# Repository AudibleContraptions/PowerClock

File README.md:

# AudibleContraptions PowerClock

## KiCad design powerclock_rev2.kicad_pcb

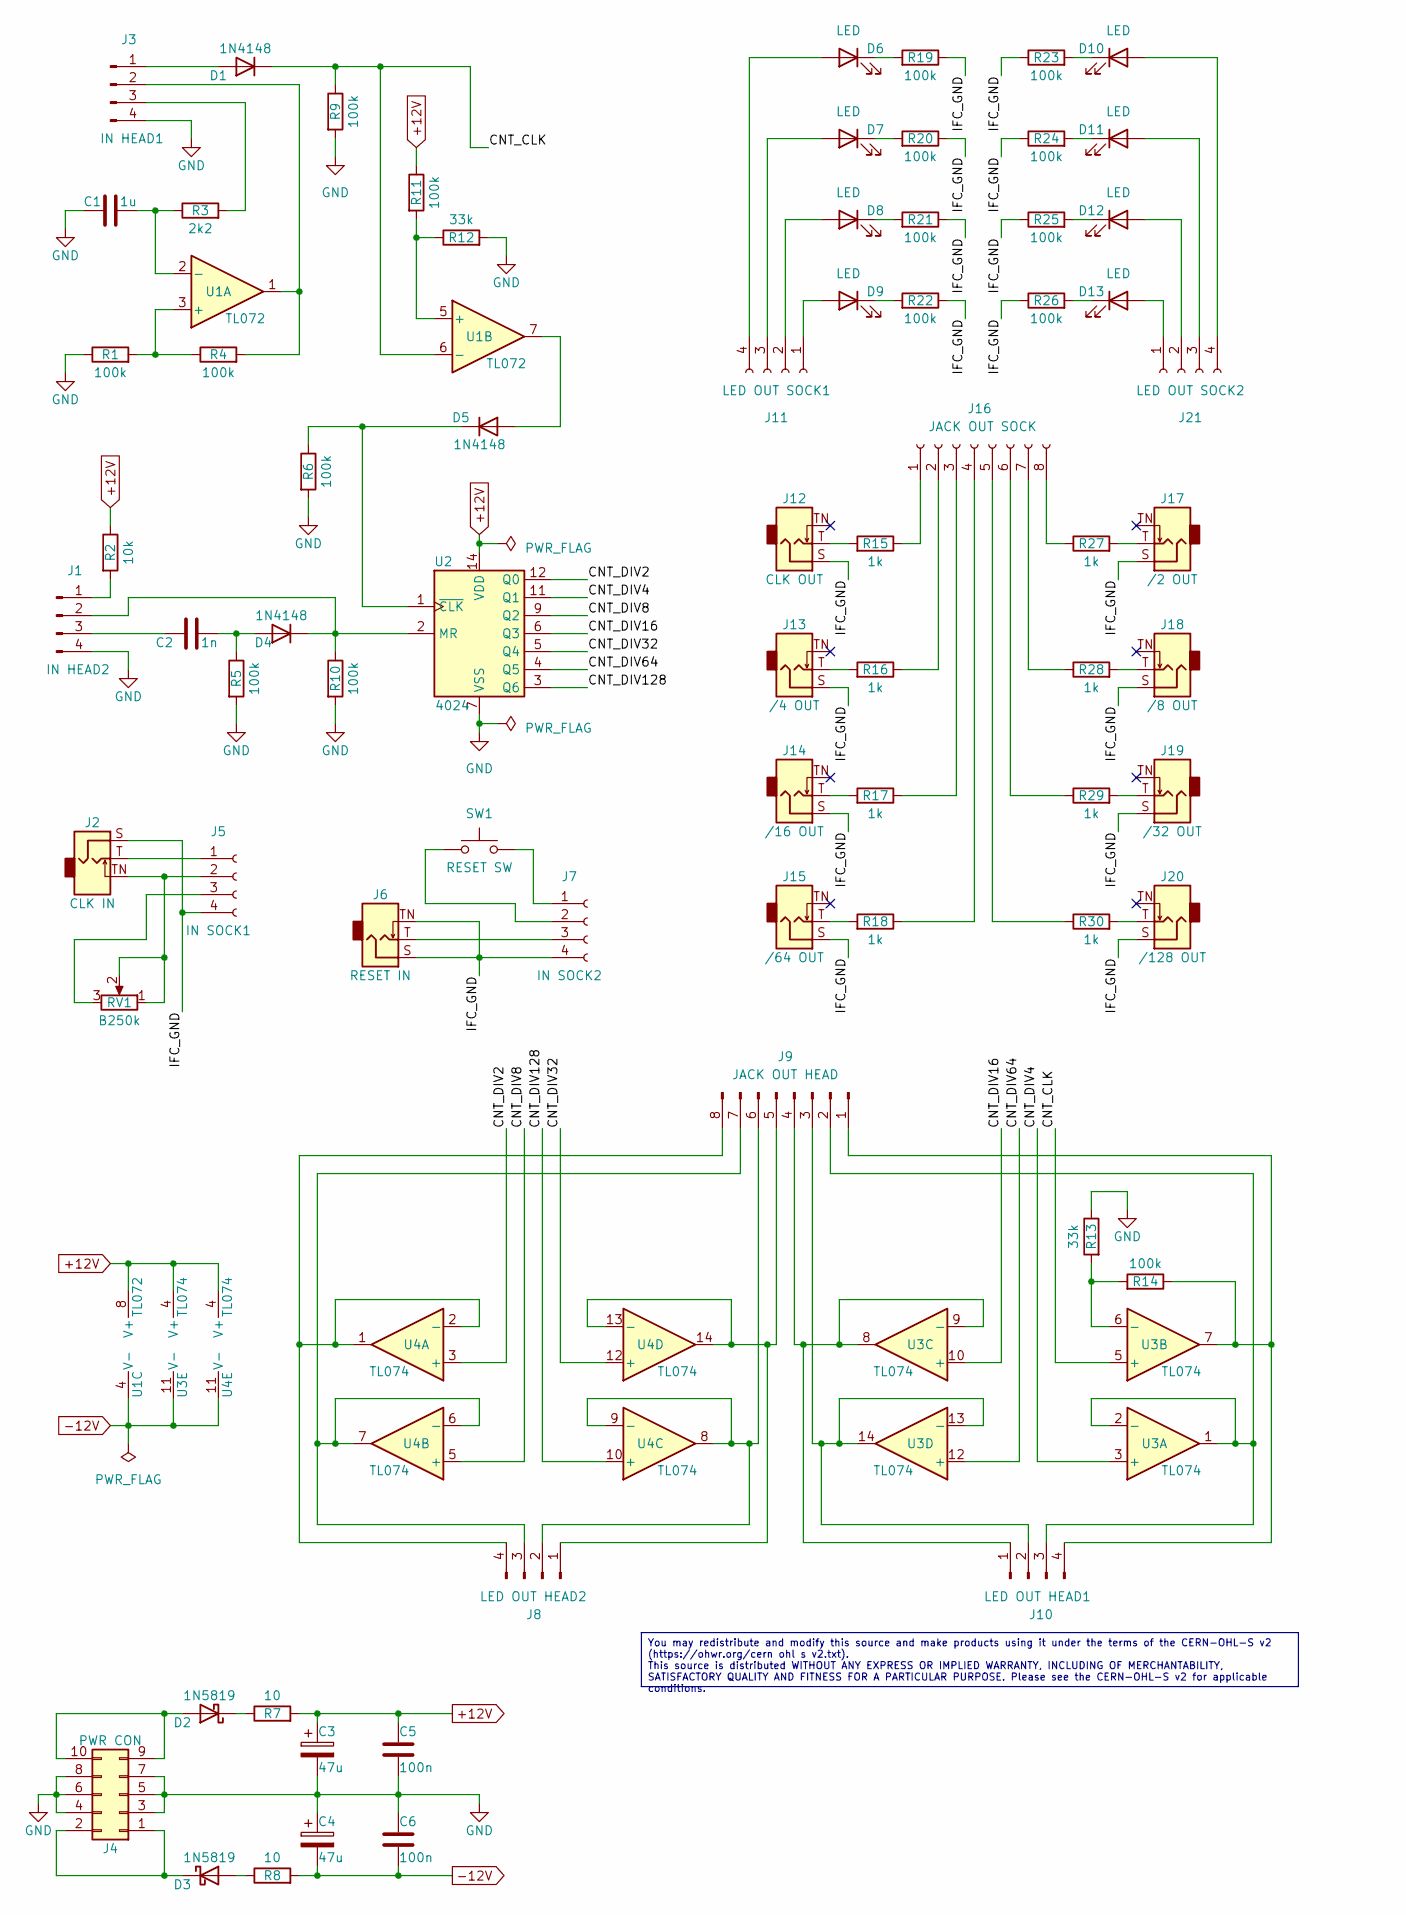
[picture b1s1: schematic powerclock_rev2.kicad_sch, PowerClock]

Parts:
C1: 1u; C_Disc_D4.3mm_W1.9mm_P5.00mm
C2: 1n; C_Disc_D4.3mm_W1.9mm_P5.00mm
C3, C4: 47u; C_Radial_D5.0mm_H11.0mm_P2.00mm
C5, C6: 100n; C_Disc_D4.3mm_W1.9mm_P5.00mm
D1, D4, D5: 1N4148; D_DO-35_SOD27_P7.62mm_Horizontal
D2, D3: 1N5819; D_DO-41_SOD81_P10.16mm_Horizontal
D6, D7, D8, D9, D10, D11, D12, D13: LED; LED_D3.0mm
J1: IN HEAD2; PinHeader_2x02_P2.54mm_Vertical
J2: CLK IN; Jack_3.5mm_QingPu_WQP-PJ398SM_Vertical_CircularHoles
J3: IN HEAD1; PinHeader_2x02_P2.54mm_Vertical
J4: PWR CON; PinHeader_2x05_P2.54mm_Vertical
J5: IN SOCK1; PinSocket_2x02_P2.54mm_Vertical
J6: RESET IN; Jack_3.5mm_QingPu_WQP-PJ398SM_Vertical_CircularHoles
J7: IN SOCK2; PinSocket_2x02_P2.54mm_Vertical
J8: LED OUT HEAD2; PinHeader_1x04_P2.54mm_Vertical
J9: JACK OUT HEAD; PinHeader_1x08_P2.54mm_Vertical
J10: LED OUT HEAD1; PinHeader_1x04_P2.54mm_Vertical
J11: LED OUT SOCK1; PinSocket_1x04_P2.54mm_Vertical
J12: CLK OUT; Jack_3.5mm_QingPu_WQP-PJ398SM_Vertical_CircularHoles
J13: /4 OUT; Jack_3.5mm_QingPu_WQP-PJ398SM_Vertical_CircularHoles
J14: /16 OUT; Jack_3.5mm_QingPu_WQP-PJ398SM_Vertical_CircularHoles
J15: /64 OUT; Jack_3.5mm_QingPu_WQP-PJ398SM_Vertical_CircularHoles
J16: JACK OUT SOCK; PinSocket_1x08_P2.54mm_Vertical
J17: /2 OUT; Jack_3.5mm_QingPu_WQP-PJ398SM_Vertical_CircularHoles
J18: /8 OUT; Jack_3.5mm_QingPu_WQP-PJ398SM_Vertical_CircularHoles
J19: /32 OUT; Jack_3.5mm_QingPu_WQP-PJ398SM_Vertical_CircularHoles
J20: /128 OUT; Jack_3.5mm_QingPu_WQP-PJ398SM_Vertical_CircularHoles
J21: LED OUT SOCK2; PinSocket_1x04_P2.54mm_Vertical
R1, R4, R5, R6, R9, R10, R11, R14, R19, R20, R21, R22, R23, R24, R25, R26: 100k; R_Axial_DIN0207_L6.3mm_D2.5mm_P7.62mm_Horizontal
R2: 10k; R_Axial_DIN0207_L6.3mm_D2.5mm_P7.62mm_Horizontal
R3: 2k2; R_Axial_DIN0207_L6.3mm_D2.5mm_P7.62mm_Horizontal
R7, R8: 10; R_Axial_DIN0207_L6.3mm_D2.5mm_P7.62mm_Horizontal
R12, R13: 33k; R_Axial_DIN0207_L6.3mm_D2.5mm_P7.62mm_Horizontal
R15, R16, R17, R18, R27, R28, R29, R30: 1k; R_Axial_DIN0207_L6.3mm_D2.5mm_P7.62mm_Horizontal
RV1: B250k; Potentiometer_Alpha_RD901F-40-00D_Single_Vertical
SW1: RESET SW; SW_PUSH_6mm
U1: TL072; DIP-8_W7.62mm_Socket
U2: 4024; DIP-14_W7.62mm_Socket
U3, U4: TL074; DIP-14_W7.62mm_Socket

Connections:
+12V: C3.1, C5.2, R2.1, R7.2, R11.1, U1.8 (V+), U2.14 (VDD), U3.4 (V+), U4.4 (V+)
-12V: C4.2, C6.1, R8.2, U1.4 (V-), U3.11 (V-), U4.11 (V-)
/CNT_CLK: D1.1 (K), R9.1, U1.6 (-), U3.5 (+)
/CNT_DIV2: U2.12 (Q0), U4.3 (+)
/CNT_DIV4: U2.11 (Q1), U3.3 (+)
/CNT_DIV8: U2.9 (Q2), U4.5 (+)
/CNT_DIV16: U2.6 (Q3), U3.10 (+)
/CNT_DIV32: U2.5 (Q4), U4.12 (+)
/CNT_DIV64: U2.4 (Q5), U3.12 (+)
/CNT_DIV128: U2.3 (Q6), U4.10 (+)
/IFC_GND: J2.S, J5.4, J6.S, J6.TN, J7.4, J12.S, J13.S, J14.S, J15.S, J17.S, J18.S, J19.S, J20.S, R19.1, R20.1, R21.1, R22.1, R23.1, R24.1, R25.1, R26.1
GND: C1.2, C3.2, C4.1, C5.1, C6.2, J1.4, J3.4, J4.3, J4.4, J4.5, J4.6, J4.7, J4.8, R1.1, R5.2, R6.2, R9.2, R10.2, R12.2, R13.1, U2.7 (VSS)
unnamed: D1.2 (A), J3.1
unnamed: D2.2 (A), J4.9, J4.10
unnamed: D2.1 (K), R7.1
unnamed: D3.2 (A), R8.1
unnamed: D3.1 (K), J4.1, J4.2
unnamed: C2.1, D4.2 (A), R5.1
unnamed: D4.1 (K), J1.2, R10.1, U2.2 (MR)
unnamed: D5.2 (A), U1.7
unnamed: D5.1 (K), R6.1, U2.1 (~CLK)
unnamed: D6.2 (A), J11.4
unnamed: D6.1 (K), R19.2
unnamed: D7.2 (A), J11.3
unnamed: D7.1 (K), R20.2
unnamed: D8.2 (A), J11.2
unnamed: D8.1 (K), R21.2
unnamed: D9.2 (A), J11.1
unnamed: D9.1 (K), R22.2
unnamed: D10.2 (A), J21.4
unnamed: D10.1 (K), R23.2
unnamed: D11.2 (A), J21.3
unnamed: D11.1 (K), R24.2
unnamed: D12.2 (A), J21.2
unnamed: D12.1 (K), R25.2
unnamed: D13.2 (A), J21.1
unnamed: D13.1 (K), R26.2
unnamed: J1.1, R2.2
unnamed: C2.2, J1.3
unnamed: J3.2, R4.2, U1.1
unnamed: J3.3, R3.2
unnamed: J2.T, J5.1
unnamed: J2.TN, J5.2, RV1.1, RV1.2
unnamed: J5.3, RV1.3
unnamed: J7.1, SW1.2
unnamed: J7.2, SW1.1
unnamed: J6.T, J7.3
unnamed: J8.1, J9.5, U4.13 (-), U4.14
unnamed: J8.2, J9.6, U4.8, U4.9 (-)
unnamed: J8.3, J9.7, U4.6 (-), U4.7
unnamed: J8.4, J9.8, U4.1, U4.2 (-)
unnamed: J9.4, J10.1, U3.8, U3.9 (-)
unnamed: J9.3, J10.2, U3.13 (-), U3.14
unnamed: J9.2, J10.3, U3.1, U3.2 (-)
unnamed: J9.1, J10.4, R14.1, U3.7
unnamed: J12.T, R15.2
unnamed: J13.T, R16.2
unnamed: J14.T, R17.2
unnamed: J15.T, R18.2
unnamed: J16.1, R15.1
unnamed: J16.2, R16.1
unnamed: J16.3, R17.1
unnamed: J16.4, R18.1
unnamed: J16.5, R30.1
unnamed: J16.6, R29.1
unnamed: J16.7, R28.1
unnamed: J16.8, R27.1
unnamed: J17.T, R27.2
unnamed: J18.T, R28.2
unnamed: J19.T, R29.2
unnamed: J20.T, R30.2
unnamed: R1.2, R4.1, U1.3 (+)
unnamed: C1.1, R3.1, U1.2 (-)
unnamed: R11.2, R12.1, U1.5 (+)
unnamed: R13.2, R14.2, U3.6 (-)

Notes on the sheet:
You may redistribute and modify this source and make products using it under the terms of the CERN-OHL-S v2 (https://ohwr.org/cern ohl s v2.txt). This source is distributed WITHOUT ANY EXPRESS OR IMPLIED WARRANTY, INCLUDING OF MERCHANTABILITY, SATISFACTORY QUALITY AND FITNESS FOR A PARTICULAR PURPO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

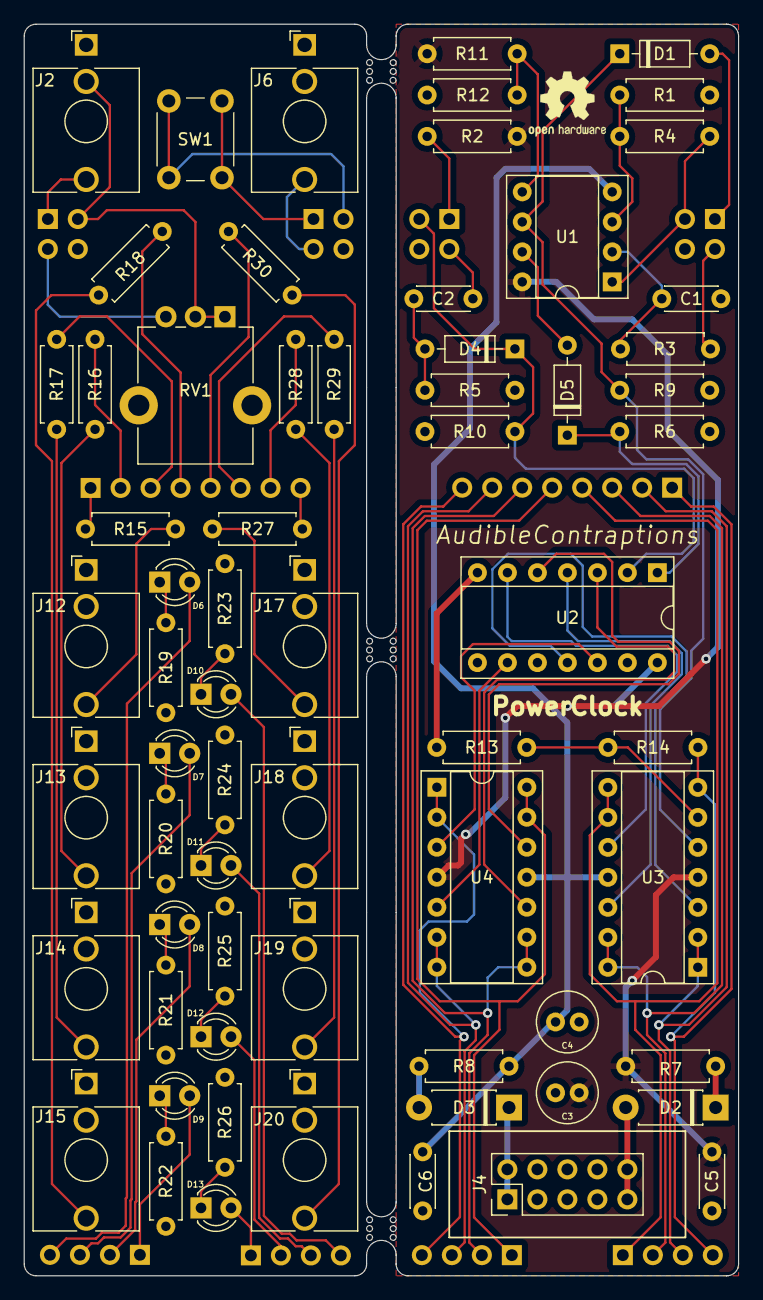
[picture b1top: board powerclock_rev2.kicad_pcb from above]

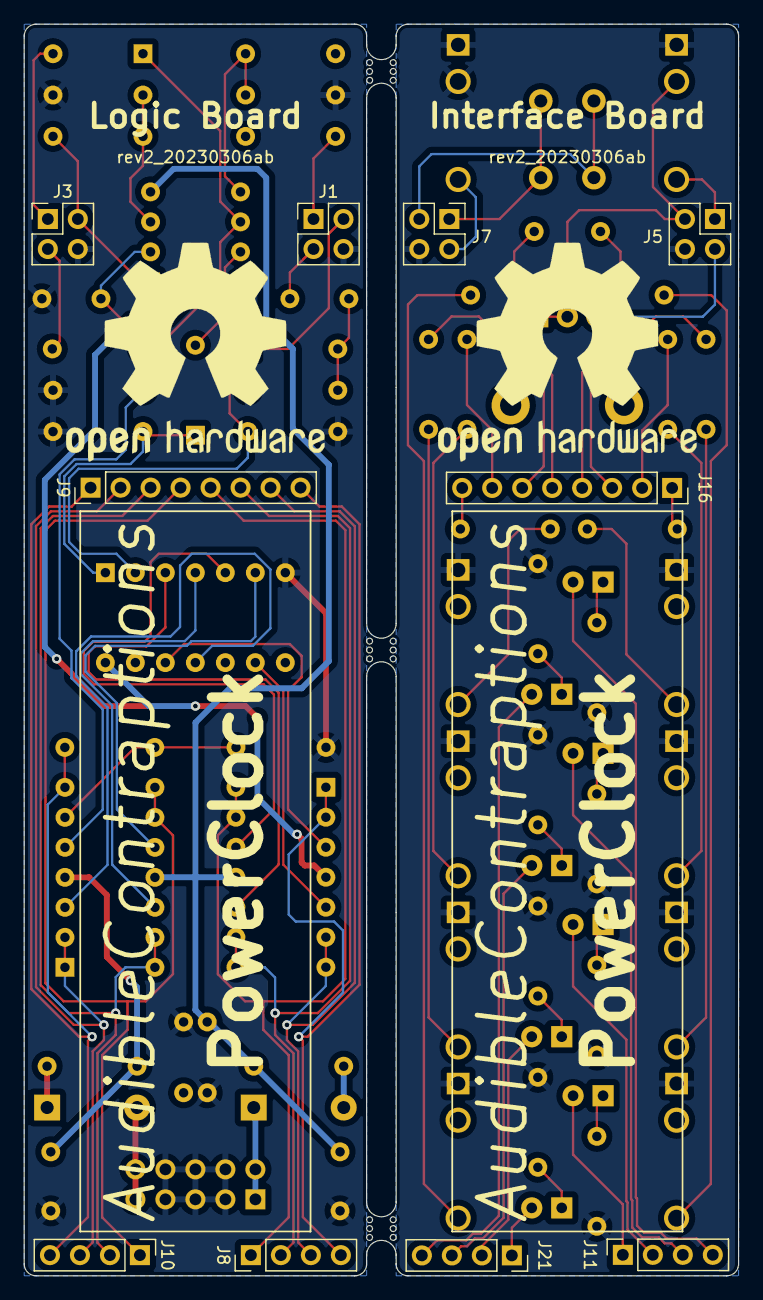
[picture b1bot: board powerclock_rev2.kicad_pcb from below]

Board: 2 copper layers, 60.5 x 106.0 mm, 76 parts (10 on the bottom side), 75 nets.

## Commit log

2023-03-09 Create LICENSE
2023-03-09 Add license disclaimers

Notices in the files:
powerclock_rev2.kicad_pcb:
This source describes Open Hardware and is licensed under the CERN-OHL-S v2 or
Copyright Arne Bethmann 2023.
